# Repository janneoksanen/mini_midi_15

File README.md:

This is a 15 button USB midi controller based on Raspberry Pi Pico. I created this project because I wanted to be able to control my NeuralDSP guitar amp simulation software. 

The hardware design is based around Raspberry Pi Pico and 6mm tactile switches. The cost to manufacture the PCB should be less than 10 USD for a batch of 5 with shipping included. Raspberry Pi Pico is about 4 USD and the switches liteally cost about a cent each. The total cost of one controller should therefore be about 6 USD and change (micro USB cable not included). 

PCB design was done using KiCad 6
https://www.kicad.org/

The software is based on CircuitPython and uses the Adafruit MIDI library.

Adafruit CircuitPython is released under MIT licence. See the details here:
https://docs.circuitpython.org/en/latest/docs/LICENSE.html?

For installation instructions see the README.txt file inside the firmware directory.

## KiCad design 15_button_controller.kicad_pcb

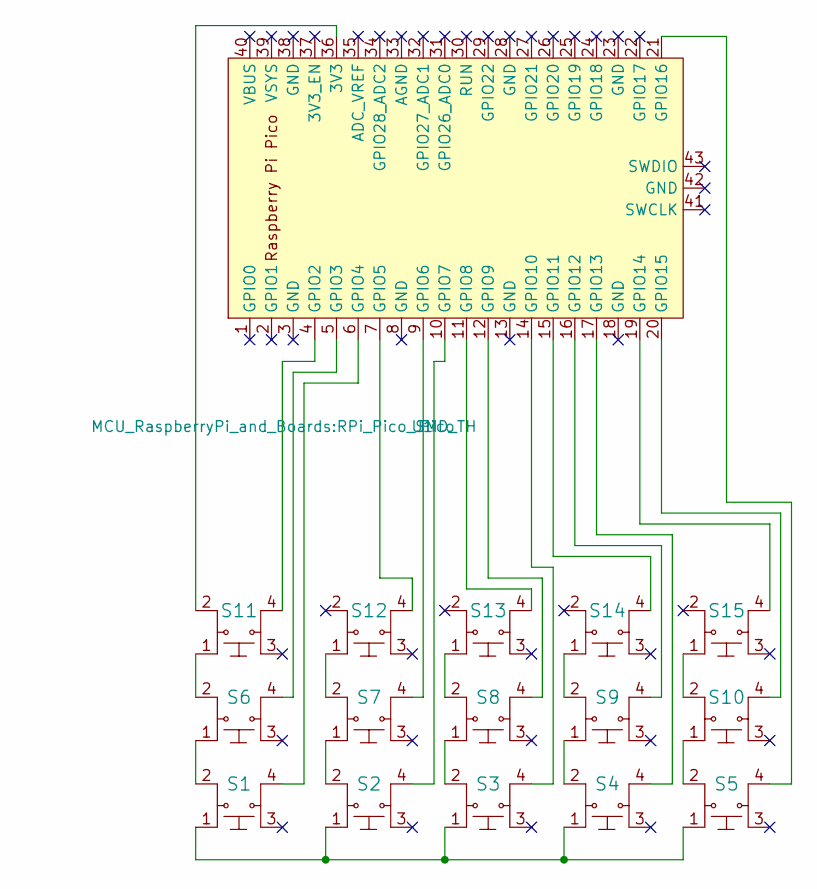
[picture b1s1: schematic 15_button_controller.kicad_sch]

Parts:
S1, S2, S3, S4, S5, S6, S7, S8, S9, S10, S11, S12, S13, S14, S15: 1825910-6; Switch_Tactile_THT_6x6mm; MPN 1825910-6; Digi-Key_PN 450-1650-ND
U1: Pico; RPi_Pico_SMD_TH

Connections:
unnamed: S1.1, S2.1, S3.1, S4.1, S5.1
unnamed: S1.2, S6.1
unnamed: S1.4, U1.6 (GPIO4)
unnamed: S2.2, S7.1
unnamed: S2.4, U1.10 (GPIO7)
unnamed: S3.2, S8.1
unnamed: S3.4, U1.14 (GPIO10)
unnamed: S4.2, S9.1
unnamed: S4.4, U1.17 (GPIO13)
unnamed: S5.4, U1.21 (GPIO16)
unnamed: S6.4, U1.5 (GPIO3)
unnamed: S7.4, U1.9 (GPIO6)
unnamed: S8.4, U1.12 (GPIO9)
unnamed: S9.4, U1.16 (GPIO12)
unnamed: S5.2, S10.1
unnamed: S10.2, S15.1
unnamed: S10.4, U1.20 (GPIO15)
unnamed: S6.2, S11.1
unnamed: S11.2, U1.36 (3V3)
unnamed: S11.4, U1.4 (GPIO2)
unnamed: S7.2, S12.1
unnamed: S12.4, U1.7 (GPIO5)
unnamed: S8.2, S13.1
unnamed: S13.4, U1.11 (GPIO8)
unnamed: S9.2, S14.1
unnamed: S14.4, U1.15 (GPIO11)
unnamed: S15.4, U1.19 (GPIO14)

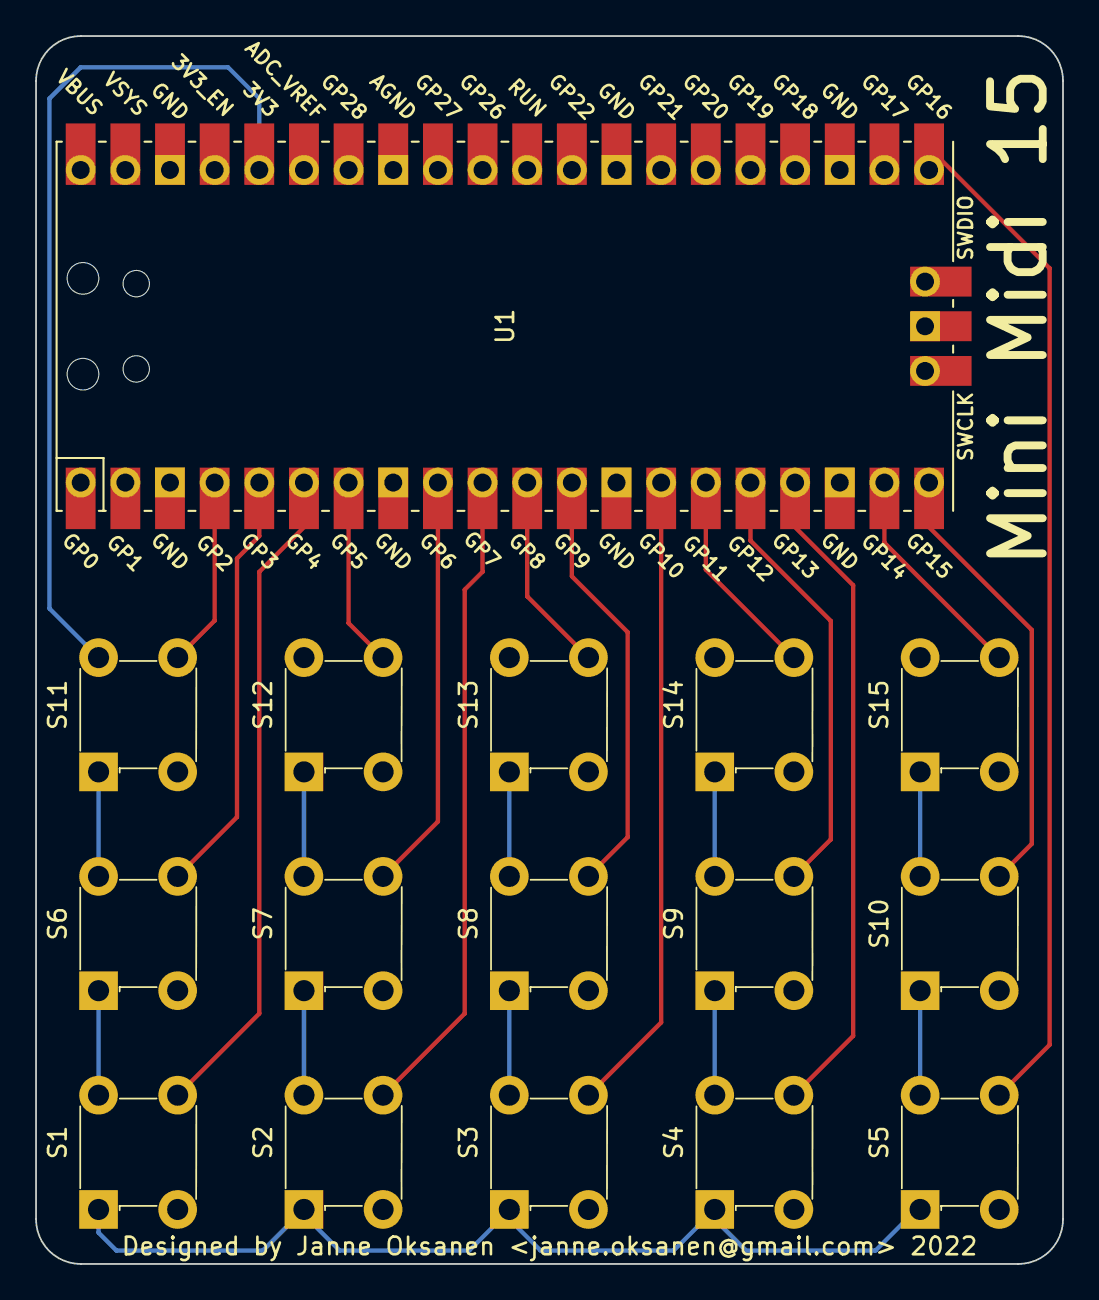
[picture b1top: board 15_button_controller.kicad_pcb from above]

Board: 2 copper layers, 58.4 x 69.8 mm, 16 parts (0 on the bottom side), 27 nets.

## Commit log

2022-10-16 Final design v1
2022-10-16 Create README.md
    Initial commit
2022-10-16 Update README.md
    Software description added
2022-10-18 Added gerber files
2022-11-10 Firmware and installation instructions added
2022-11-10 Added a 3D rendering of the PCB
2022-11-10 Removed backups
2022-11-10 Removed cache file
